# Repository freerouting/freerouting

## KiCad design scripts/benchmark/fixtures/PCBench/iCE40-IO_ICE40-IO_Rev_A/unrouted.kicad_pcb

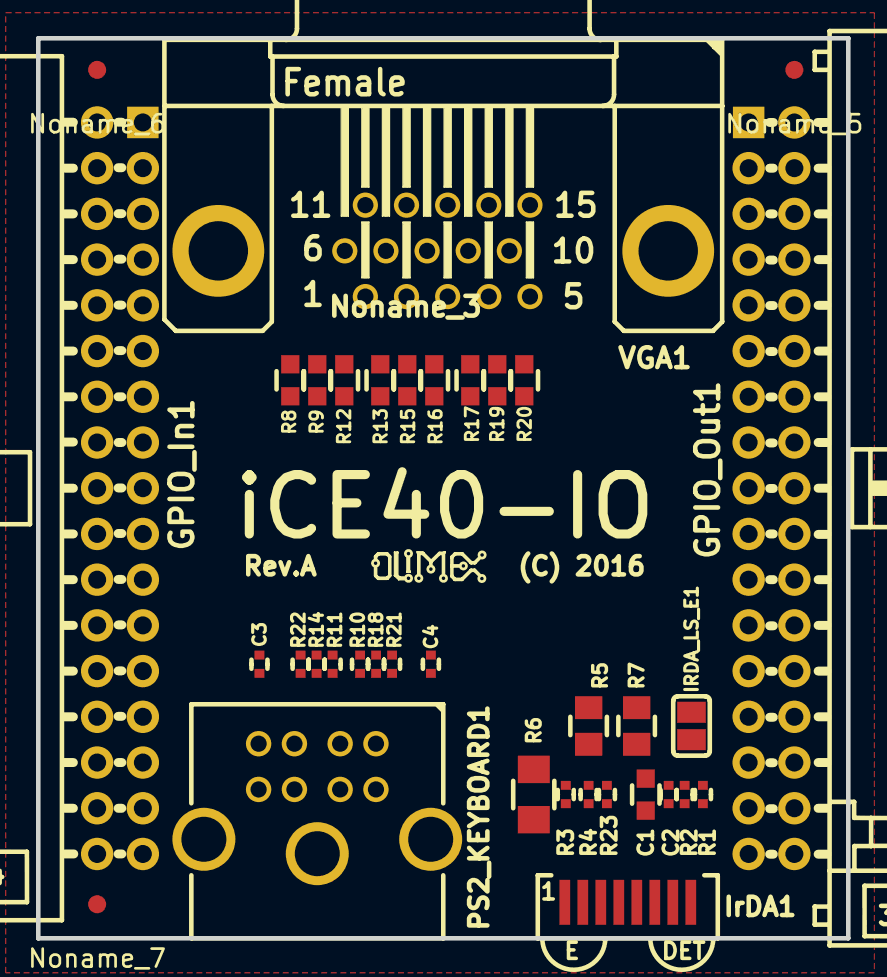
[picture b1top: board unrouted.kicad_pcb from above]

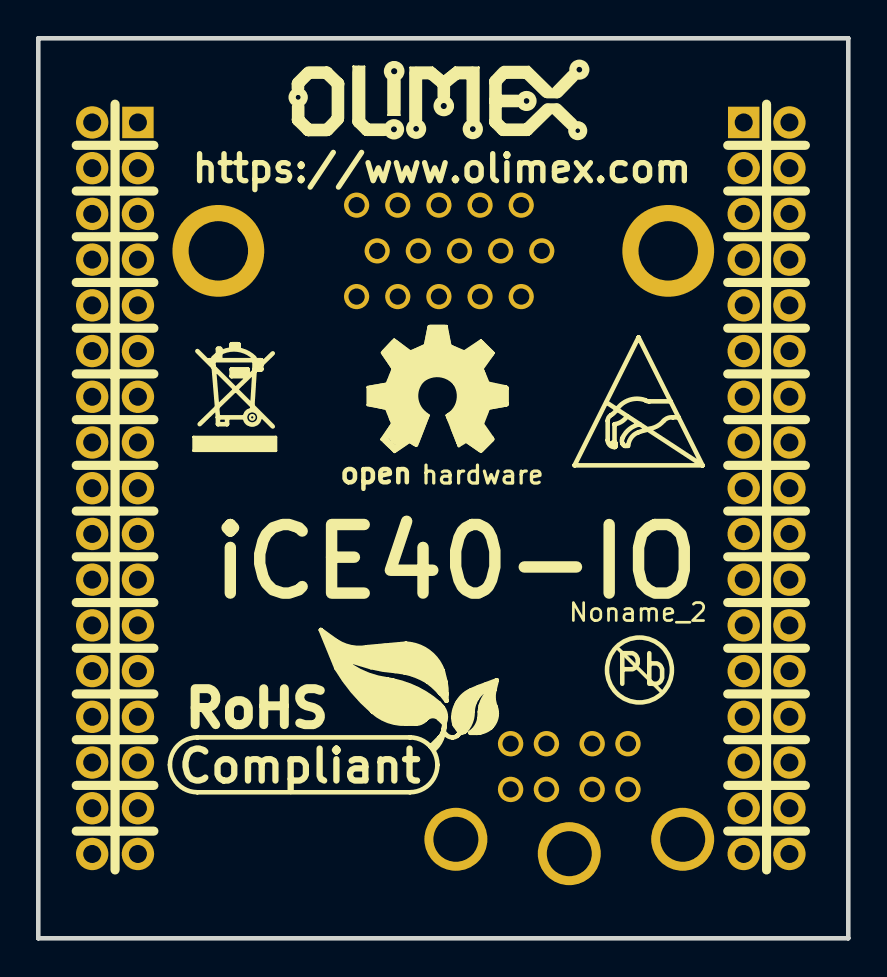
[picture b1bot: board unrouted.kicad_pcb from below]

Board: 2 copper layers, 45.0 x 50.0 mm, 43 parts (6 on the bottom side), 43 nets, no tracks yet.

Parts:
C1: 22uF/6.3V; C_0603_5MIL_DWS
C2, C3: 100nF; C_0402_5MIL_DWS
C4: 10nF; C_0402_5MIL_DWS
GPIO_In1: IDC34R; IDC34R_PCB
GPIO_Out1: BH34R
IRDA_LS_E1: Opened; SJ
IrDA1: TFDU4100; TFDU4100_PACK
Noname_1: LOGO_RECYCLEBIN_1
Noname_2: LOGO_PBFREE
Noname_3: OLIMEX_LOGO_SMALL_TB
Noname_4: OLIMEX_LOGO_TB
Noname_5, Noname_6, Noname_7: Fiducial1x3
Noname_8: LOGO_OPENHARDWARE_8x8
PS2_KEYBOARD1: MDR6_MINI-DIN; PS2_MDR6_MINI-DIN
R1, R4, R23: NA; R_0402_5MIL_DWS
R2, R21, R22: 10k; R_0402_5MIL_DWS
R3: NA(10k); R_0402_5MIL_DWS
R5, R7: 47R; R_0805_5MIL_DWS
R6: 15R; R_1206_5MIL_DWS
R8, R13, R17: 470R; C_0603_5MIL_DWS
R9, R15, R19: 1k; C_0603_5MIL_DWS
R10, R11: 5.6k; R_0402_5MIL_DWS
R12, R16, R20: 1.8k; C_0603_5MIL_DWS
R14, R18: 200R; R_0402_5MIL_DWS
Ref**: Val**; LOGO_ANTISTATIC_1
Ref**_2: Val**; LOGO_ROHS_1
VGA1: VGA15-F(CD0515S21J0)

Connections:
+3V3: GPIO_In1.3, GPIO_Out1.3, R2.2, R4.2, R6.2, R7.2
+5V: C3.2, GPIO_In1.1, GPIO_Out1.1, PS2_KEYBOARD1.4, R10.1, R11.1
/EXTCLK: GPIO_In1.6, GPIO_Out1.6
/GPIO_Pin<5>: GPIO_In1.5, GPIO_Out1.5
/GPIO_Pin<7>: GPIO_In1.7, GPIO_Out1.7
/GPIO_Pin<9>: GPIO_In1.9, GPIO_Out1.9
/GPIO_Pin<11>: GPIO_In1.11, GPIO_Out1.11
/GPIO_Pin<13>: GPIO_In1.13, GPIO_Out1.13
/GPIO_Pin<15>: GPIO_In1.15, GPIO_Out1.15
/GPIO_Pin<17>: GPIO_In1.17, GPIO_Out1.17
/GPIO_Pin<19>: GPIO_In1.19, GPIO_Out1.19
/GPIO_Pin<21>: GPIO_In1.21, GPIO_Out1.21
/GPIO_Pin<23>: GPIO_In1.23, GPIO_Out1.23
/GPIO_Pin<25>: GPIO_In1.25, GPIO_Out1.25
/GPIO_Pin<31>: GPIO_In1.31, GPIO_Out1.31
/IrDA_Rx: GPIO_In1.12, GPIO_Out1.12, IrDA1.3, R3.1
/IrDA_SC: GPIO_In1.10, GPIO_Out1.10, R1.1
/IrDA_Tx: GPIO_In1.33, GPIO_Out1.33, R5.1
/PS2_CLK: GPIO_In1.14, GPIO_Out1.14, R10.2, R18.1, R21.1
/PS2_DATA: GPIO_In1.16, GPIO_Out1.16, R11.2, R14.1, R22.1
/VGA_BLUE1: GPIO_In1.26, GPIO_Out1.26, R17.1
/VGA_BLUE2: GPIO_In1.24, GPIO_Out1.24, R19.1
/VGA_BLUE3: GPIO_In1.22, GPIO_Out1.22, R20.1
/VGA_GREEN1: GPIO_In1.32, GPIO_Out1.32, R13.1
/VGA_GREEN2: GPIO_In1.30, GPIO_Out1.30, R15.1
/VGA_GREEN3: GPIO_In1.28, GPIO_Out1.28, R16.1
/VGA_HSYNC: GPIO_In1.20, GPIO_Out1.20, VGA1.13
/VGA_RED1: GPIO_In1.27, GPIO_Out1.27, R8.1
/VGA_RED2: GPIO_In1.29, GPIO_Out1.29, R9.1
/VGA_RED3: GPIO_In1.34, GPIO_Out1.34, R12.1
/VGA_VSYNC: GPIO_In1.18, GPIO_Out1.18, VGA1.14
GND: C1.1, C2.1, C3.1, C4.1, GPIO_In1.2, GPIO_In1.4, GPIO_In1.8, GPIO_Out1.2, GPIO_Out1.4, GPIO_Out1.8, IRDA_LS_E1.2, IrDA1.8, PS2_KEYBOARD1.3, R3.2, R21.2, R22.2, VGA1.5, VGA1.6, VGA1.7, VGA1.8, VGA1.9, VGA1.10, VGA1.16, VGA1.17
unnamed: C1.2, C2.2, IrDA1.6, R7.1
unnamed: C4.2, PS2_KEYBOARD1.9
unnamed: IRDA_LS_E1.1, IrDA1.7, R1.2, R2.1, R23.2
unnamed: IrDA1.1, R6.1
unnamed: IrDA1.4, R4.1, R5.2
unnamed: IrDA1.5, R23.1
unnamed: PS2_KEYBOARD1.1, R14.2
unnamed: PS2_KEYBOARD1.5, R18.2
unnamed: R8.2, R9.2, R12.2, VGA1.1
unnamed: R13.2, R15.2, R16.2, VGA1.2
unnamed: R17.2, R19.2, R20.2, VGA1.3

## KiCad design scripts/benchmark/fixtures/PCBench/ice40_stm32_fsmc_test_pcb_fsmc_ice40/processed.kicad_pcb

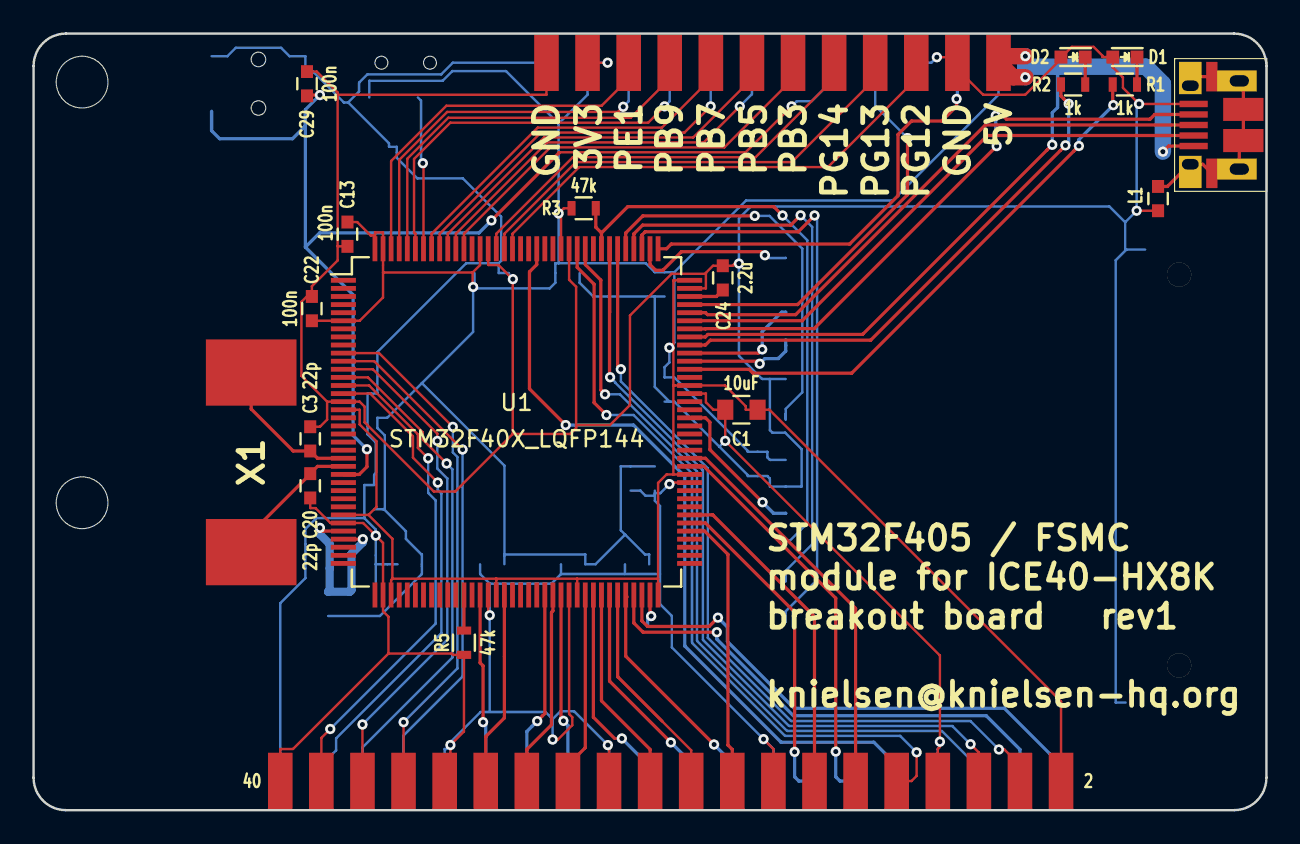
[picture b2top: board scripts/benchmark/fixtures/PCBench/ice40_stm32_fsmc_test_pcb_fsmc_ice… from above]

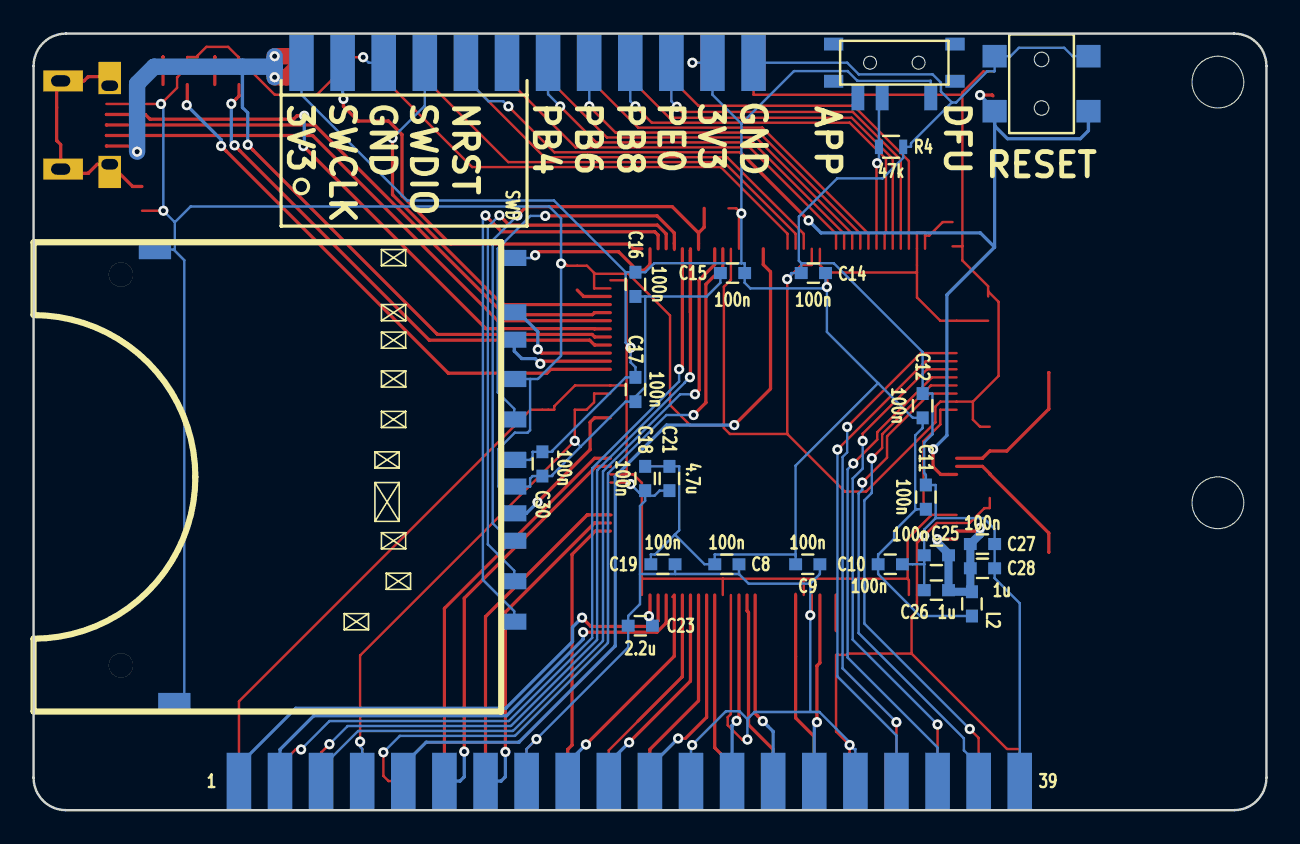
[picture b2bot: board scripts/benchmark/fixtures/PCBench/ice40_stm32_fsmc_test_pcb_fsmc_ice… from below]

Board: 2 copper layers, 76.2 x 48.0 mm, 42 parts (23 on the bottom side), 70 nets.

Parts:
B1: SWITCH_4PIN; pushbutton_EVQ_PSR02K
C1: 10uF; C_0805
C3, C20: 22p; C_0603
C8, C9, C10, C11, C12, C13, C14, C15, C16, C17, C18, C19, C22, C25, C27, C29, C30: 100n; C_0603
C21: 4.7u; C_0603
C23, C24: 2.2u; C_0603
C26, C28: 1u; C_0603
D1: SML-211UTT86; LED_0603
D2: SML-211YTT86; LED_0603
L1: 30@100MHz; C_0603
L2: 22@100MHz; C_0603
P1: SD_CARD; SD_CARD_10100
P2: CONN_02X20; ice40_vert_conn
P5: CONN_02X12; ice40_top_conn_12
P7: KNUSB; 10103594-0001LF
R1, R2: 1k; R_0603
R3, R4, R5: 47k; R_0603
SW1: SWITCH_INV; switch_msk_12c02
U1: STM32F40X_LQFP144; LQFP-144_20x20mm_Pitch0.5mm
X1: CRYSTAL; 2-SOJ

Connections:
+3.3V: C1.1, C8.2, C9.2, C10.2, C11.2, C12.2, C13.2, C14.2, C15.2, C16.2, C17.2, C18.2, C19.2, C21.2, C22.1, C30.1, L2.1, P1.4, P2.2, P5.3, P5.4, P5.23, R3.1, SW1.1, U1.6, U1.17, U1.30, U1.39, U1.52, U1.62, U1.72, U1.84, U1.95, U1.108, U1.121, U1.131, U1.143, U1.144
/3V3_adc: C25.1, C26.1, C27.1, C28.1, L2.2, U1.32, U1.33
/boot0: R4.1, SW1.2, U1.138
/boot1: R5.2, U1.48
/fpga_io1: P2.3, U1.69
/fpga_io2: P2.1, U1.70
/nrst: B1.1, B1.2, C29.1, P5.15, U1.25
/osc_in: C3.1, U1.23, X1.2
/osc_out: C20.1, U1.24, X1.1
/pb3: P5.14, U1.133
/pb4: P5.11, U1.134
/pb5: P5.12, U1.135
/pb6: P5.9, U1.136
/pb7: P5.10, U1.137
/pb8: P5.7, U1.139
/pb9: P5.8, U1.140
/pe0: P5.5, U1.141
/pe1: P5.6, U1.142
/pg12: P5.20, U1.127
/pg13: P5.18, U1.128
/pg14: P5.16, U1.129
/sd_cd: P1.10, U1.91
/sd_clk: P1.5, U1.113
/sd_cmd: P1.2, R3.2, U1.116
/sd_d0: P1.7, U1.98
/sd_d1: P1.8, U1.99
/sd_d2: P1.9, U1.111
/sd_d3: P1.1, U1.112
/sd_wp: P1.11, U1.110
/sram2_ce: P2.9, U1.124
/sram_a0: P2.34, U1.10
/sram_a1: P2.33, U1.11
/sram_a2: P2.36, U1.12
/sram_a3: P2.35, U1.13
/sram_a4: P2.38, U1.14
/sram_a5: P2.37, U1.15
/sram_a6: P2.29, U1.50
/sram_a7: P2.30, U1.53
/sram_d0: P2.11, U1.85
/sram_d1: P2.12, U1.86
/sram_d2: P2.4, U1.114
/sram_d3: P2.6, U1.115
/sram_d4: P2.27, U1.58
/sram_d5: P2.28, U1.59
/sram_d6: P2.25, U1.60
/sram_d7: P2.26, U1.63
/sram_d8: P2.21, U1.64
/sram_d9: P2.22, U1.65
/sram_d10: P2.19, U1.66
/sram_d11: P2.20, U1.67
/sram_d12: P2.17, U1.68
/sram_d13: P2.18, U1.77
/sram_d14: P2.13, U1.78
/sram_d15: P2.14, U1.79
/sram_oe: P2.5, U1.118
/sram_we: P2.10, U1.119
/swclk: P5.21, U1.109
/swdio: P5.17, U1.105
/usb_5v: P5.24, P7.1, U1.101
/usb_dm: P7.2, U1.103
/usb_dp: P7.3, U1.104
/usb_id: P7.4, U1.102
/user_led1: R1.1, U1.97
/user_led2: R2.1, U1.100
GND: B1.3, B1.4, C1.2, C3.2, C8.1, C9.1, C10.1, C11.1, C12.1, C13.1, C14.1, C15.1, C16.1, C17.1, C18.1, C19.1, C20.2, C21.1, C22.2, C23.2, C24.2, C25.2, C26.2, C27.2, C28.2, C29.2, C30.2, D1.2, D2.2, L1.1, P1.3, P1.6, P1.12, P2.7, P2.8, P2.15, P2.16, P2.23, P2.24, P2.31, P2.32, P2.39, P2.40, P5.1, P5.2, P5.19, P5.22, P7.5, R4.2, R5.1, U1.16, U1.31, U1.38, U1.51, U1.61, U1.83, U1.94, U1.107, U1.120, U1.130
unnamed: C23.1, U1.71
unnamed: C24.1, U1.106
unnamed: D1.1, R1.2
unnamed: D2.1, R2.2
unnamed: L1.2, P7.6

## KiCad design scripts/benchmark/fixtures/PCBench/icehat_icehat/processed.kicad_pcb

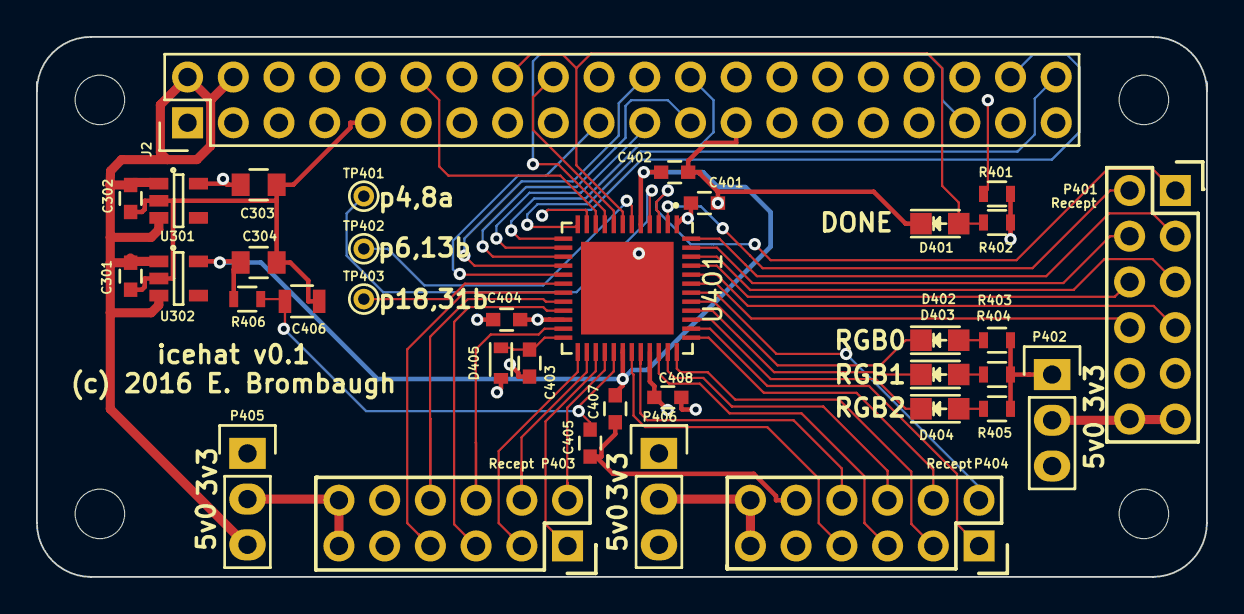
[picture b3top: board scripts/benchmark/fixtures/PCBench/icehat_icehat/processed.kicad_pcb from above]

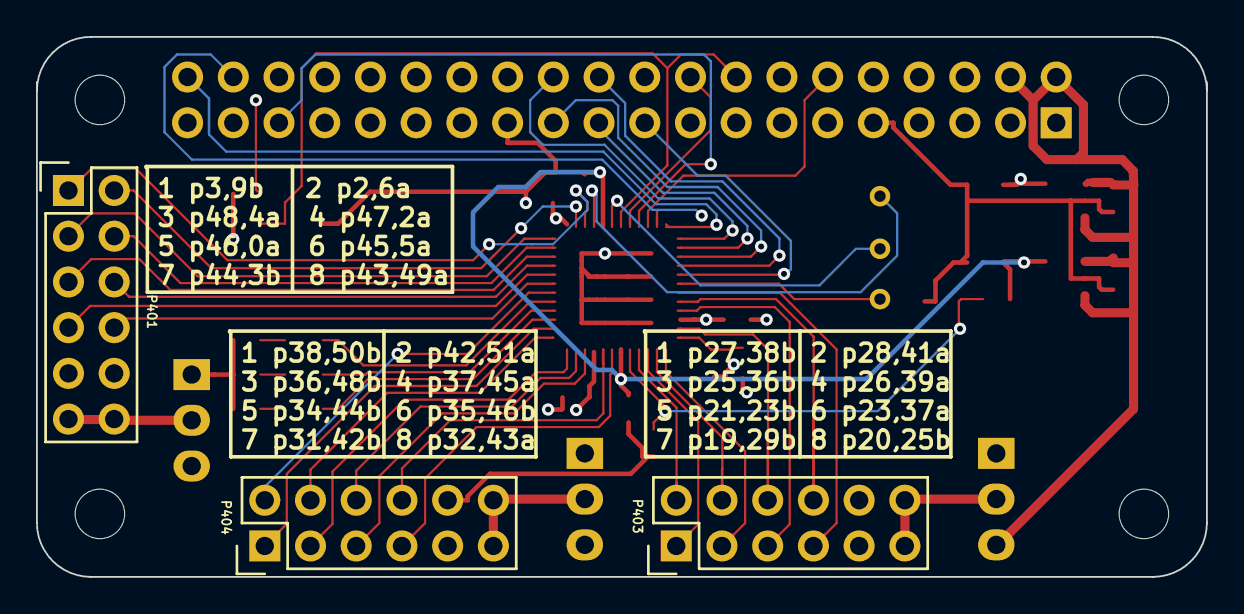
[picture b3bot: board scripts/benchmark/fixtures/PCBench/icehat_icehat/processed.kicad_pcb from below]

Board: 4 copper layers, 65.0 x 30.0 mm, 40 parts (3 on the bottom side), 53 nets.

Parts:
C301, C302: 1uf; C_0603
C303, C304: 10uf; C_0805
C401, C402, C403, C404, C405, C407, C408: 0.1uf; C_0603
C406: 10uf; R_0805
D401, D402, D403, D404: LED; LED_0805
D405: D; D_0603
J2: RPi_GPIO; Pin_Header_Straight_2x20
Noname_1, Noname_2, Noname_3, Noname_4: RPi_Hat_Mounting_Hole
P401, P403, P404: CONN_02X06; Pin_Header_Straight_2x06
P402, P405, P406: CONN_01X03; Pin_Header_Straight_1x03
R401, R406: 10k; R_0603
R402, R403, R404, R405: 2.2k; R_0603
TP401, TP402, TP403: CONN_01X01; PINTST
U301: MCP1802-3.3; SOT-23-5
U302: MCP1802-1.2; SOT-23-5
U401: ice5lp4k_sg48; QFN-48-1EP_7x7mm_Pitch0.5mm_DIY_PADS

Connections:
+1V2: C304.1, C402.1, C407.1, R406.2, U302.5, U401.5, U401.30
+3V3: C303.1, C401.1, C404.1, C408.1, D405.2, P402.1, P405.1, P406.1, R401.1, R402.1, R403.1, R404.1, R405.1, U301.5, U401.1, U401.22, U401.33
+5V: C301.1, C302.1, J2.2, J2.4, P402.3, P405.3, P406.3, U301.1, U301.3, U302.1, U302.3
GND: C301.2, C302.2, C303.2, C304.2, C401.2, C402.2, C403.2, C404.2, C405.2, C406.2, C407.2, C408.2, D401.1, J2.6, J2.9, J2.14, J2.20, J2.25, J2.30, J2.34, J2.39, P401.9, P401.10, P403.9, P403.10, P404.9, P404.10, U301.2, U302.2, U401.49
GPIO23_CDN: D401.2, J2.16, R402.2, U401.7
GPIO24_CRS: J2.18, R401.2, U401.8
GPIO25_SS: J2.22, U401.16
I2S_BCLK: J2.12, U401.10
I2S_DI: J2.38, U401.11
I2S_DO: J2.40, U401.12
I2S_LRCK: J2.35, U401.9
unnamed: C403.1, D405.1, U401.24
unnamed: C405.1, C406.1, R406.1, U401.29
unnamed: D402.1, U401.41
unnamed: D402.2, R403.2
unnamed: D403.1, U401.40
unnamed: D403.2, R404.2
unnamed: D404.1, U401.39
unnamed: D404.2, R405.2
unnamed: P401.1, U401.3
unnamed: P401.2, U401.2
unnamed: P401.3, U401.48
unnamed: P401.4, U401.47
unnamed: P401.5, U401.46
unnamed: P401.6, U401.45
unnamed: P401.7, U401.44
unnamed: P401.8, U401.43
unnamed: P401.11, P401.12, P402.2
unnamed: P403.1, U401.27
unnamed: P403.2, U401.28
unnamed: P403.3, U401.25
unnamed: P403.4, U401.26
unnamed: P403.5, U401.21
unnamed: P403.6, U401.23
unnamed: P403.7, U401.19
unnamed: P403.8, U401.20
unnamed: P403.11, P403.12, P405.2
unnamed: P404.1, U401.38
unnamed: P404.2, U401.42
unnamed: P404.3, U401.36
unnamed: P404.4, U401.37
unnamed: P404.5, U401.34
unnamed: P404.6, U401.35
unnamed: P404.7, U401.31
unnamed: P404.8, U401.32
unnamed: P404.11, P404.12, P406.2
unnamed: TP401.1, U401.4
unnamed: TP402.1, U401.6
unnamed: TP403.1, U401.18
SPI_CE0: J2.24, U401.13
SPI_CLK: J2.23, U401.15
SPI_MISO: J2.21, U401.14
SPI_MOSI: J2.19, U401.17

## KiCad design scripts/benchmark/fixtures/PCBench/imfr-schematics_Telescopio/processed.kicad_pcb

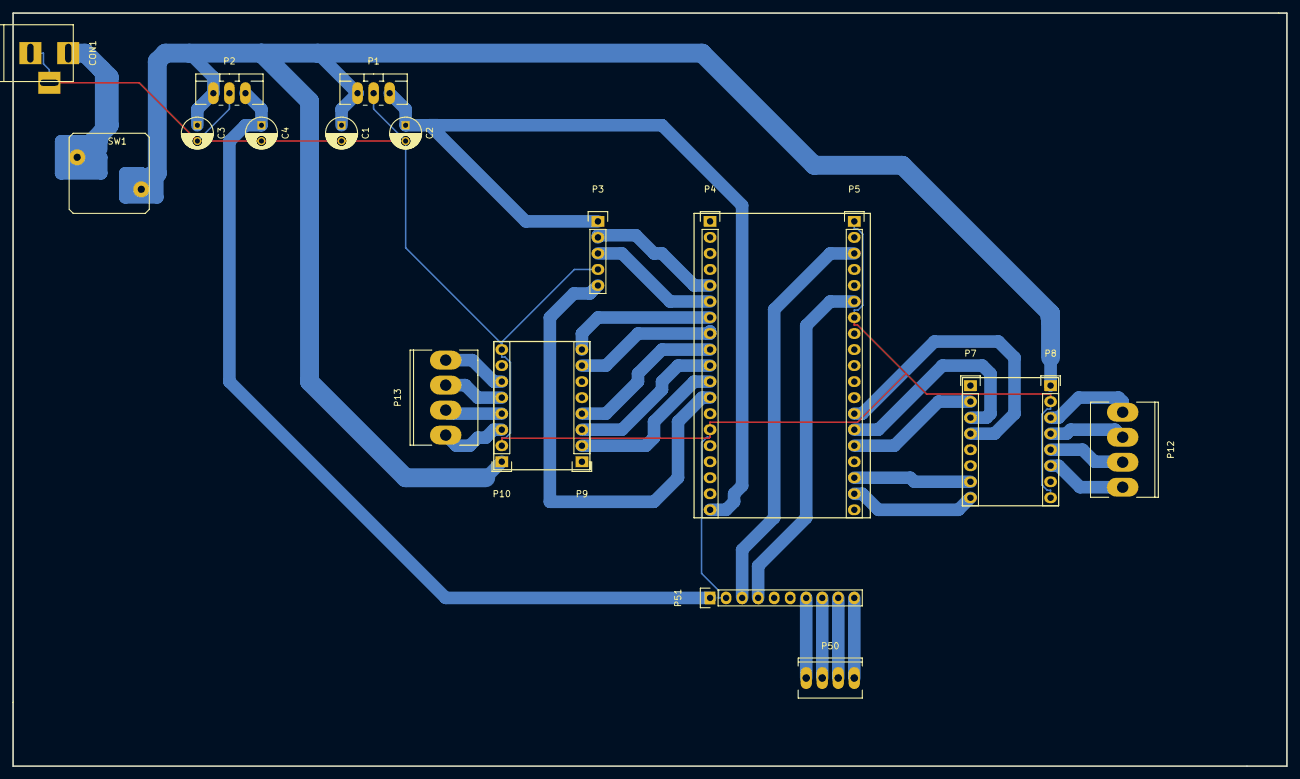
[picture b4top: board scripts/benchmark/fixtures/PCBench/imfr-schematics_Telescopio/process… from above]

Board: 2 copper layers, 201.9 x 119.4 mm, 19 parts (0 on the bottom side), 32 nets.

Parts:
C1, C2, C3, C4: C; C_Radial_D5_L11_P2.5
CON1: BARREL_JACK
P1, P2: CONN_01X03; TO-220_Neutral123_Vertical_LargePads
P3: CONN_01X05; Pin_Header_Straight_1x05
P4, P5: CONN_01X19; Pin_Header_Straight_1x19
P7, P8, P9, P10: CONN_01X08; Pin_Header_Straight_1x08
P12, P13: CONN_01X04; Socket_MOLEX-KK-RM3-96mm_Lock_4pin_straight
P50: CONN_01X04; Socket_MOLEX-KK-RM2-54mm_Lock_4pin_straight
P51: CONN_01X10; Pin_Header_Straight_1x10
SW1: SW_PUSH

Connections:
/3v3: C4.1, P2.3, P51.1
/5v: C2.1, P1.3, P3.1, P4.19
/24v: CON1.1, SW1.1
/24v_Sal: C1.1, C3.1, P1.1, P2.1, P8.1, P10.1, SW1.2
/A0: P50.1, P51.7
/A1: P50.2, P51.8
/A2: P50.3, P51.9
/A3: P50.4, P51.10
/A11: P8.5, P12.3
/A12: P10.5, P13.3
/A21: P8.6, P12.4
/A22: P10.6, P13.4
/B11: P8.4, P12.2
/B12: P10.4, P13.2
/B21: P8.3, P12.1
/B22: P10.3, P13.1
/Dir_1: P5.18, P7.8
/Dir_2: P4.7, P9.8
/INT_IMU: P3.5, P4.12
/M0_1: P5.15, P7.2
/M0_2: P4.11, P9.2
/M1_1: P5.14, P7.3
/M1_2: P4.10, P9.3
/M2_1: P5.13, P7.4
/M2_2: P4.9, P9.4
/SCL: P5.3, P51.3
/SCL_2: P3.2, P4.5
/SDA: P5.6, P51.4
/SDA_2: P3.3, P4.6
/Step_1: P5.17, P7.7
/Step_2: P4.8, P9.7
GND: C1.2, C2.2, C3.2, C4.2, CON1.2, CON1.3, P1.2, P2.2, P3.4, P4.14, P5.1, P5.7, P8.2, P8.8, P10.2, P10.8, P51.2

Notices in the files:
scripts/benchmark/fixtures/PCBench/iCE40-IO_ICE40-IO_Rev_A/unrouted.kicad_pcb:
(C) 2016
scripts/benchmark/fixtures/PCBench/icehat_icehat/processed.kicad_pcb:
(c) 2016 E. Brombaugh
